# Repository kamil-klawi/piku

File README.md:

# Dwukolorowa lampa ostrzegawcza

Projekt zrealizowany w ramach przedmiotu **Projektowanie i konstrukcja urządzeń** na Uniwersytecie Morskim w Gdyni.

## Opis projektu

Prezentowany układ to elektroniczny moduł sygnalizacyjny, który symuluje działanie świateł ostrzegawczych (tzw. "koguta policyjnego"). Konstrukcja opiera się na układach scalonych NE555 oraz CD4017. Efektem działania urządzenia jest naprzemienne błyskanie dwóch grup diod LED w kolorze niebieskim oraz czerwonym. Zastosowanie potencjometru pozwala na płynną regulację częstotliwości błysków.

---

## Wykaz elementów

*Tabela 1. Tabela elemento w zastosowanych w układzie*

| Nazwa elementu | Ilość | Oznaczenia |
| :--- | :---: | :--- |
| Rezystor 10kΩ | 3 | R1, R2, R3 |
| Rezystor 100Ω | 2 | R4, R5 |
| Potencjometr | 1 | RW |
| Kondensator elektrolityczny 10µF | 1 | C1 |
| Kondensator ceramiczny 10nF | 1 | C2 |
| Dioda 1N4148 | 6 | D1-D6 |
| Czerwona dioda LED | 12 | D7-D18 |
| Niebieska dioda LED | 12 | D19-D30 |
| Tranzystor 8050 | 2 | Q1, Q2 |
| Układ scalony NE555 | 1 | U1 |
| Układ scalony CD4017 | 1 | U2 |
| Podstawka pod układ NE555 | 1 | U1 |
| Podstawka pod układ CD4017 | 1 | U2 |
| Przewód montażowy czerwony 10cm | 1 | - | 
| Przewód montażowy czarny 10cm | 1 | - |

---

## Schemat elektryczny, mozaika ścieżek i maska na folii

<figure>
  
  <figcaption align="center"><em>Rysunek 1. Schemat elektryczny w programie Eagle</em></figcaption>
</figure>

<figure>
  
  <figcaption align="center"><em>Rysunek 2. Mozaika ścieżek w programie Eagle</em></figcaption>
</figure>

<figure>
  
  <figcaption align="center"><em>Rysunek 3. Maska na folii</em></figcaption>
</figure>

---

## Płytka przed i po konstrukcji

<table width="100%">
  <tr>
    <td align="center" width="50%">
      
      <br>
      <em>Rysunek 4. Płytka po wywołaniu</em>
    </td>
    <td align="center" width="50%">
      
      <br>
      <em>Rysunek 5. Płytka po wytrawieniu</em>
    </td>
  </tr>
</table>

<table width="100%">
  <tr>
    <td align="center" width="50%">
      
      <br>
      <em>Rysunek 6. Widok płytki PCB po montażu warstwa górna</em>
    </td>
    <td align="center" width="50%">
      
      <br>
      <em>Rysunek 7. Widok płytki PCB po montażu strona ścieżki</em>
    </td>
  </tr>
</table>

---

## Wnioski

<table width="100%">
  <tr>
    <td align="center" width="50%">
      
      <br>
      <em>Rysunek 8. Prezentacja działania zmontowanego układu faza aktywności diod LED czerwonych</em>
    </td>
    <td align="center" width="50%">
      
      <br>
      <em>Rysunek 9. Prezentacja działania zmontowanego układu faza aktywności diod LED niebieskich</em>
    </td>
  </tr>
</table>

Na podstawie przeprowadzonych testów laboratoryjnych stwierdzono, że zmontowany układ elektroniczny działa w pełni poprawnie i zgodnie z założeniami projektowymi. Urządzenie bezproblemowo przełącza się pomiędzy fazą aktywności diod LED czerwonych (Rys. 8) a fazą aktywności diod LED niebieskich (Rys. 9).

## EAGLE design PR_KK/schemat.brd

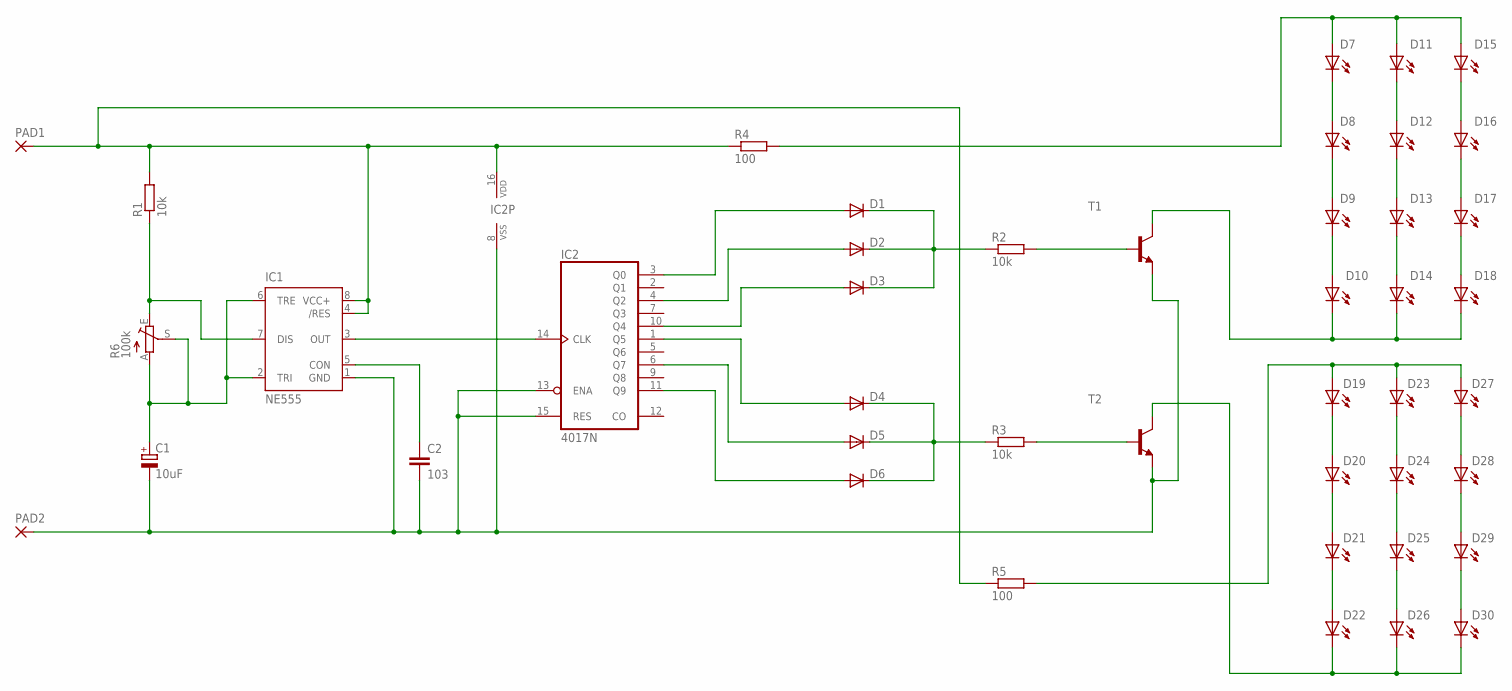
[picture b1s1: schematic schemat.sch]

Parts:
C1: 10uF; E2-4
C2: 103; C025-024X044
D1, D2, D3, D4, D5, D6: 1N4148DO35-7; DO35-7
D7, D8, D9, D10, D11, D12, D13, D14, D15, D16, D17, D18, D19, D20, D21, D22, D23, D24, D25, D26, D27, D28, D29, D30: LED5MM
IC1: NE555; DIL-08
IC2: 4017N; DIL16
PAD1, PAD2: WIREPAD3,17/1,3; 3,17/1,3
R1, R2, R3: 10k; 0207/7
R4, R5: 100; 0207/7
R6: 100k; CA6V
T1, T2: -NPN-TO92; TO92

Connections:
unnamed: D4.C, D5.C, D6.C, R3.1
unnamed: D6.A, IC2.11 (Q9)
unnamed: D5.A, IC2.6 (Q7)
unnamed: D4.A, IC2.1 (Q5)
unnamed: D3.A, IC2.10 (Q4)
unnamed: D2.A, IC2.4 (Q2)
unnamed: D1.A, IC2.3 (Q0)
unnamed: D1.C, D2.C, D3.C, R2.1
unnamed: R2.2, T1.2 (B)
unnamed: R3.2, T2.2 (B)
unnamed: D10.K (C), D14.K (C), D18.K (C), T1.3 (C)
unnamed: D22.K (C), D26.K (C), D30.K (C), T2.3 (C)
unnamed: IC1.4 (/RES), IC1.8 (VCC+), IC2.16 (VDD), PAD1.1, R1.2, R4.1, R5.1
unnamed: D19.A, D23.A, D27.A, R5.2
unnamed: D27.K (C), D28.A
unnamed: D28.K (C), D29.A
unnamed: D29.K (C), D30.A
unnamed: D21.K (C), D22.A
unnamed: D20.K (C), D21.A
unnamed: D19.K (C), D20.A
unnamed: D23.K (C), D24.A
unnamed: D24.K (C), D25.A
unnamed: D25.K (C), D26.A
unnamed: D17.K (C), D18.A
unnamed: D13.K (C), D14.A
unnamed: D9.K (C), D10.A
unnamed: D7.K (C), D8.A
unnamed: D11.K (C), D12.A
unnamed: D15.K (C), D16.A
unnamed: D16.K (C), D17.A
unnamed: D12.K (C), D13.A
unnamed: D8.K (C), D9.A
unnamed: D7.A, D11.A, D15.A, R4.2
unnamed: IC1.7 (DIS), R1.1, R6.E
unnamed: C1.+, IC1.2 (TRI), IC1.6 (TRE), R6.A, R6.S
unnamed: C2.1, IC1.5 (CON)
unnamed: C1.-, C2.2, IC1.1 (GND), IC2.8 (VSS), IC2.13 (ENA), IC2.15 (RES), PAD2.1, T1.1 (E), T2.1 (E)
unnamed: IC1.3 (OUT), IC2.14 (CLK)

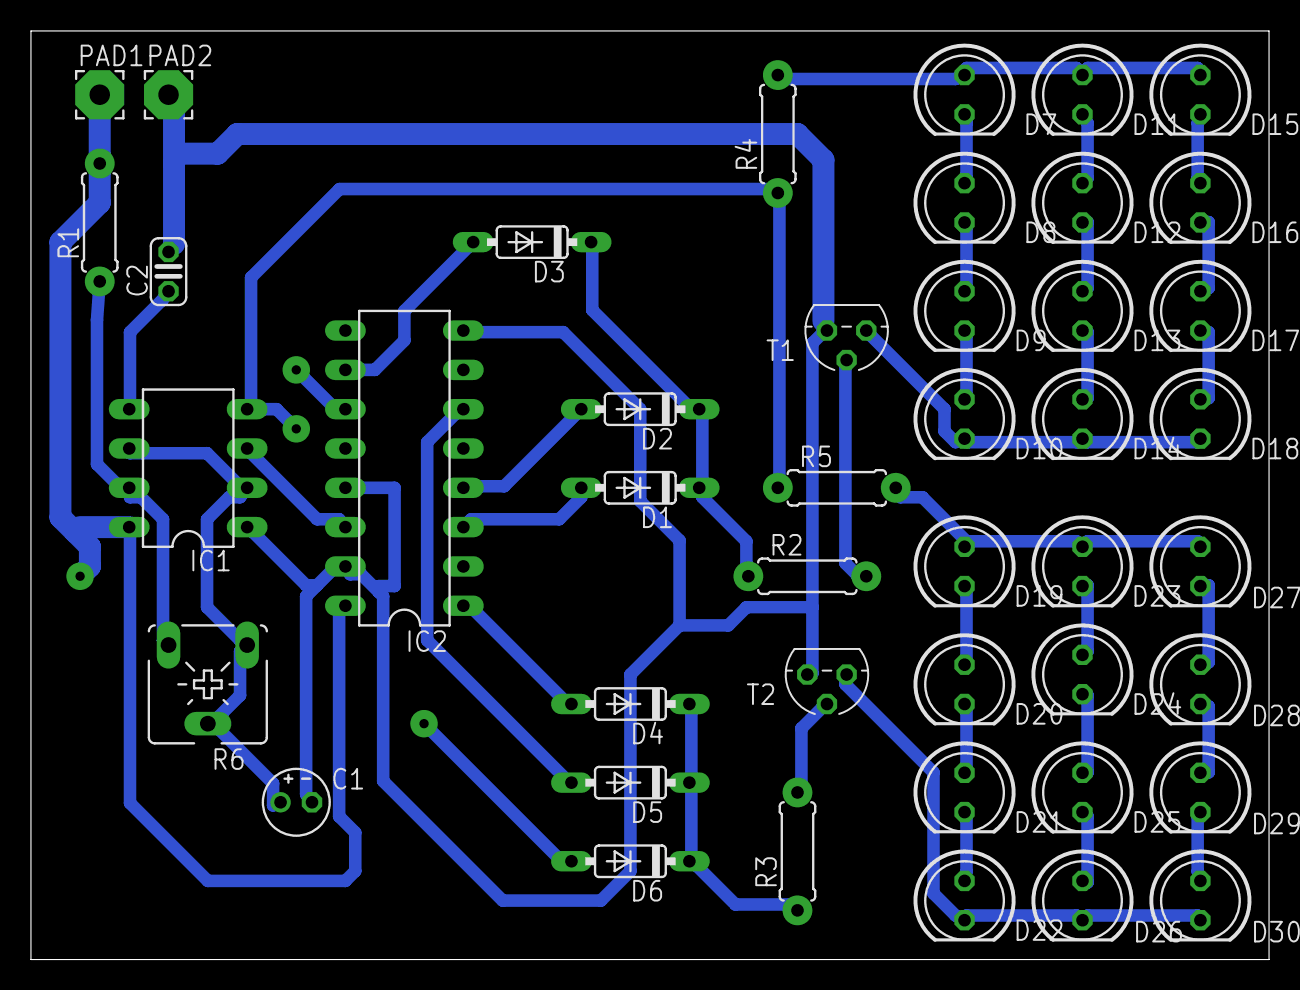
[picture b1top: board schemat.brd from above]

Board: 2 copper layers, 80.0 x 60.0 mm, 44 parts (0 on the bottom side), 38 nets.
